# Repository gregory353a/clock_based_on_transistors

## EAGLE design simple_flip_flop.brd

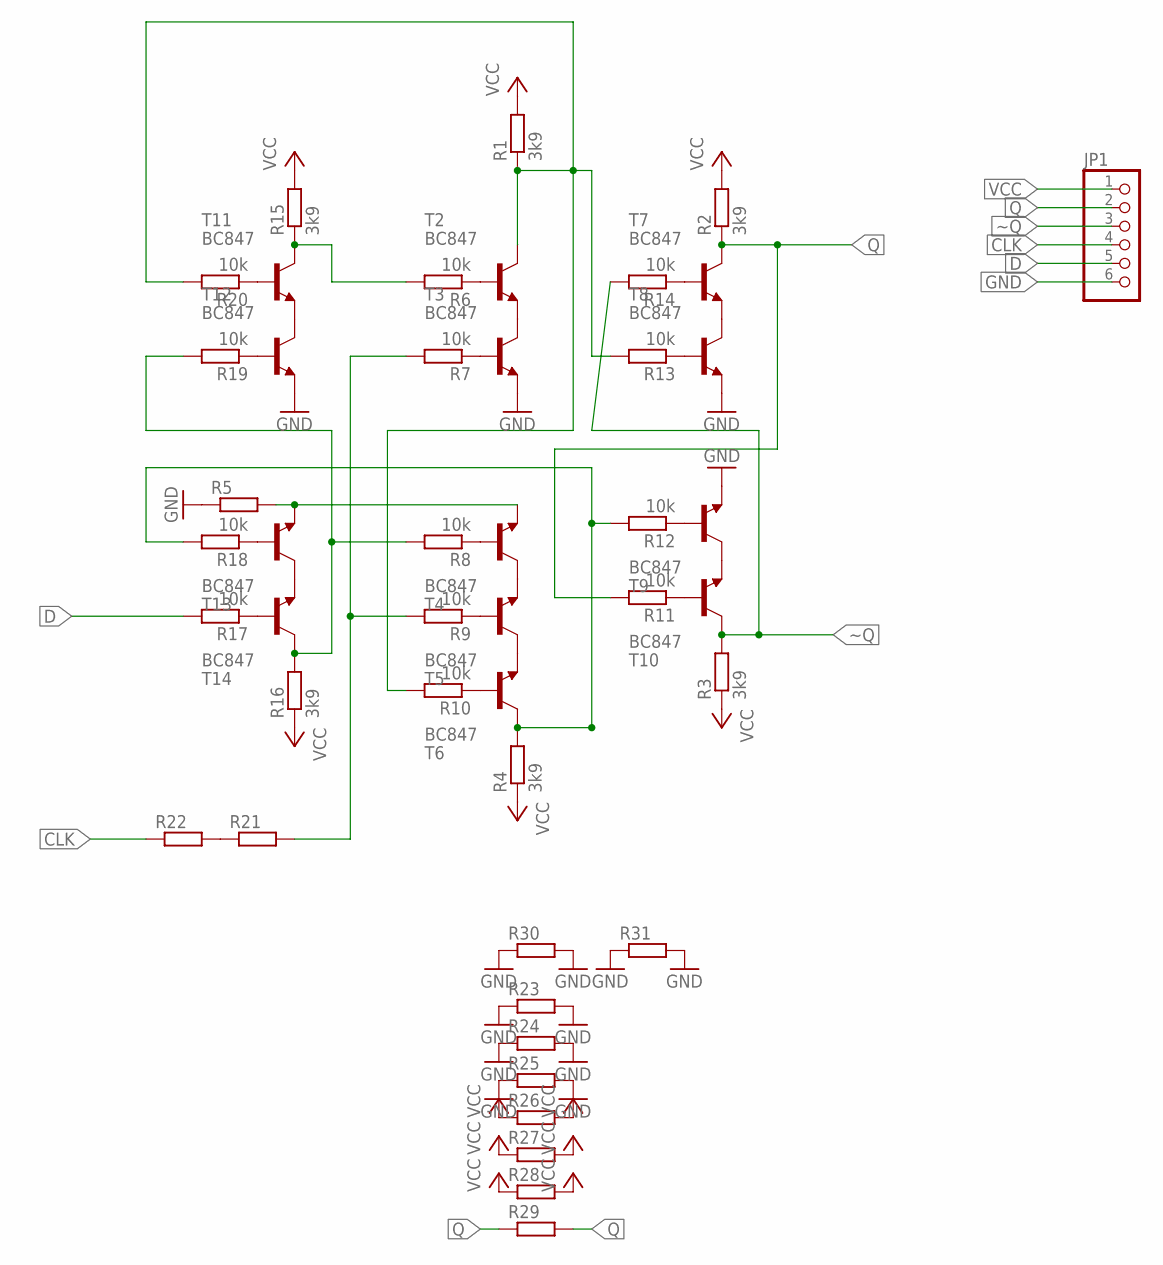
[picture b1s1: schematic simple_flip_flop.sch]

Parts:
JP1: PINHD-1X06_2.54-SMD; 1X06SMD
R1, R2, R3, R4, R15, R16: 3k9; R0805W
R5, R21, R22, R23, R24, R25, R26, R27, R28, R29, R30, R31: R-EU_R1206; R1206
R6, R7, R8, R9, R10, R11, R12, R13, R14, R17, R18, R19, R20: 10k; R0805W
T2, T3, T4, T5, T6, T7, T8, T9, T10, T11, T12, T13, T14: BC847; SOT23

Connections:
CLK: JP1.4, R22.1
D: JP1.5, R17.2
GND: JP1.6, R5.1, R23.1, R23.2, R24.1, R24.2, R25.1, R25.2, R30.1, R30.2, R31.1, R31.2, T3.2 (E), T8.2 (E), T9.2 (E), T12.2 (E)
unnamed: R5.2, T4.2 (E), T13.2 (E)
unnamed: T2.2 (E), T3.3 (C)
unnamed: T4.3 (C), T5.2 (E)
unnamed: T5.3 (C), T6.2 (E)
unnamed: T7.2 (E), T8.3 (C)
unnamed: T9.3 (C), T10.2 (E)
unnamed: R1.1, R10.2, R13.2, R20.2, T2.3 (C)
unnamed: R21.1, R22.2
unnamed: R4.2, R12.2, R18.2, T6.3 (C)
unnamed: R6.1, T2.1 (B)
unnamed: R7.1, T3.1 (B)
unnamed: R8.1, T4.1 (B)
unnamed: R9.1, T5.1 (B)
unnamed: R10.1, T6.1 (B)
unnamed: R11.1, T10.1 (B)
unnamed: R12.1, T9.1 (B)
unnamed: R13.1, T8.1 (B)
unnamed: R14.1, T7.1 (B)
unnamed: T11.2 (E), T12.3 (C)
unnamed: T13.3 (C), T14.2 (E)
unnamed: R6.2, R15.1, T11.3 (C)
unnamed: R8.2, R16.2, R19.2, T14.3 (C)
unnamed: R17.1, T14.1 (B)
unnamed: R18.1, T13.1 (B)
unnamed: R19.1, T12.1 (B)
unnamed: R20.1, T11.1 (B)
Q: JP1.2, R2.1, R11.2, R29.1, R29.2, T7.3 (C)
S%9: R7.2, R9.2, R21.2
VCC: JP1.1, R1.2, R2.2, R3.1, R4.1, R15.2, R16.1, R26.1, R26.2, R27.1, R27.2, R28.1, R28.2
~Q: JP1.3, R3.2, R14.2, T10.3 (C)

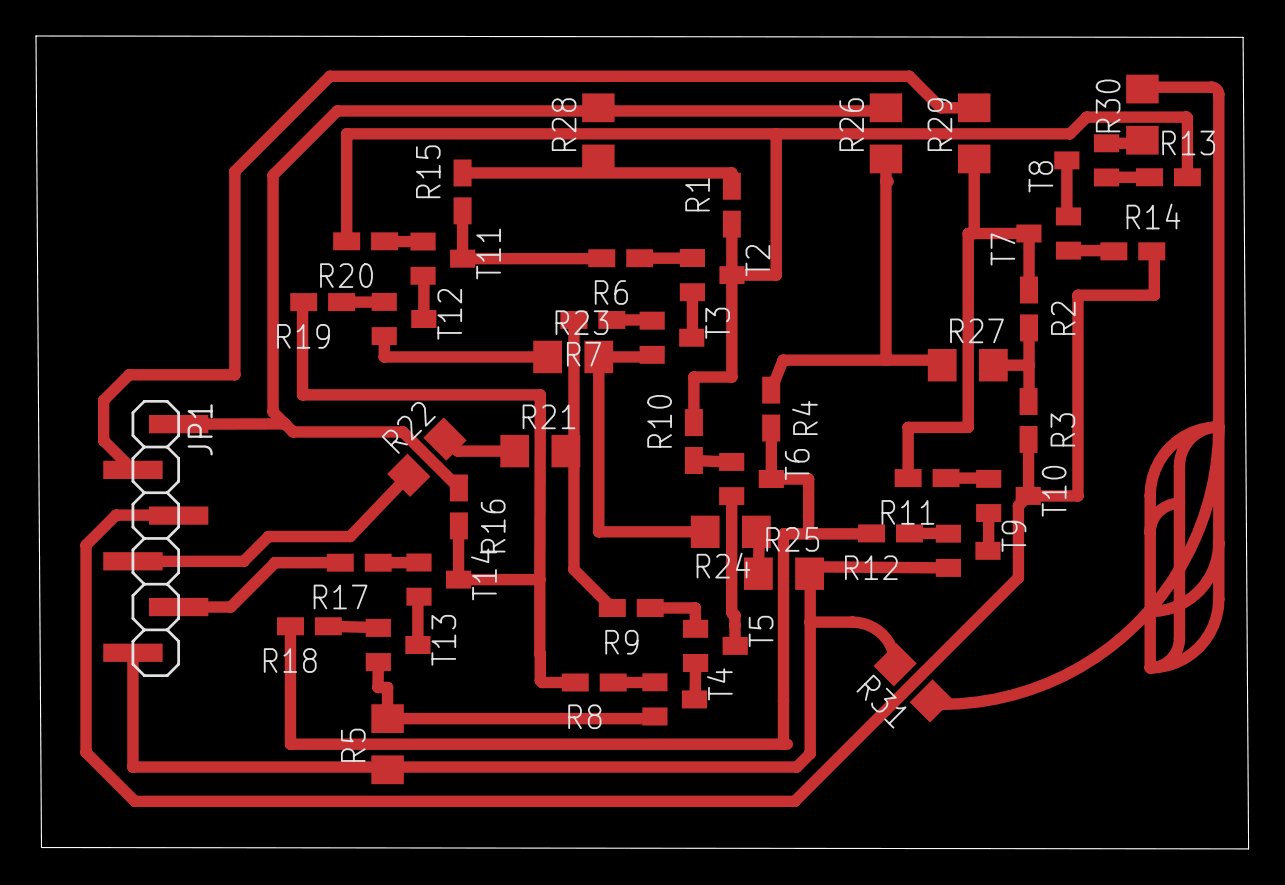
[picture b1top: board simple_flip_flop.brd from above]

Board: 2 copper layers, 67.4 x 45.2 mm, 45 parts (0 on the bottom side), 33 nets.

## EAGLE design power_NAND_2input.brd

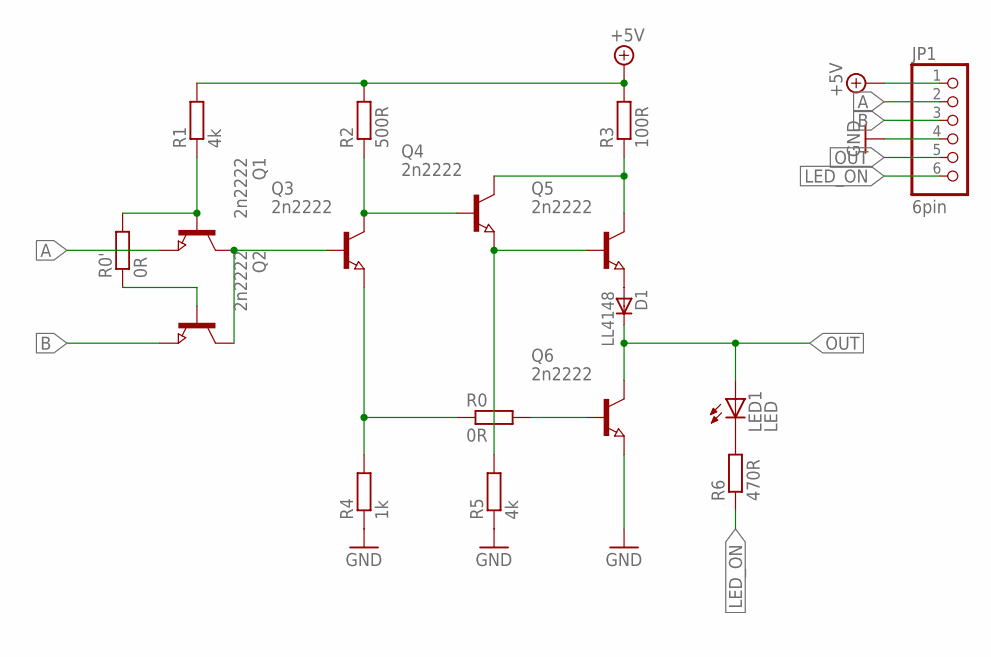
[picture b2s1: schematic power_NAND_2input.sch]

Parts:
D1: LL4148; SOD80_DO213AA_MINIMELF
JP1: 6pin; 1X06SMD/90
LED1: LED; CHIPLED_0805
Q1, Q2, Q3, Q4, Q5, Q6: 2n2222; SOT23
R0, R0': 0R; R1206
R1, R5: 4k; R0805
R2: 500R; R0805
R3: 100R; R0805
R4: 1k; R0805
R6: 470R; R0805

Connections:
+5V: JP1.1, R1.2, R2.2, R3.2
A: JP1.2, Q1.2 (E)
B: JP1.3, Q2.2 (E)
GND: JP1.4, Q6.2 (E), R4.1, R5.1
LED_ON: JP1.6, R6.1
unnamed: Q1.3 (C), Q2.3 (C), Q3.1 (B)
unnamed: Q1.1 (B), R0'.2, R1.1
unnamed: Q3.3 (C), Q4.1 (B), R2.1
unnamed: Q3.2 (E), R0.1, R4.2
unnamed: Q4.3 (C), Q5.3 (C), R3.1
unnamed: Q4.2 (E), Q5.1 (B), R5.2
unnamed: D1.A, Q5.2 (E)
unnamed: Q2.1 (B), R0'.1
unnamed: LED1.C, R6.2
unnamed: Q6.1 (B), R0.2
OUT: D1.C, JP1.5, LED1.A, Q6.3 (C)

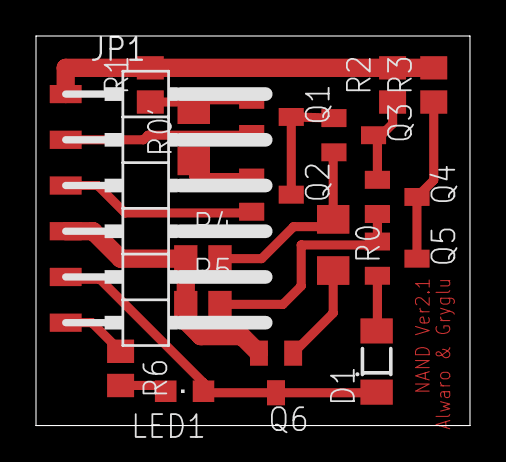
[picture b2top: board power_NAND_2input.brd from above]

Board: 2 copper layers, 24.1 x 21.6 mm, 17 parts (0 on the bottom side), 16 nets.

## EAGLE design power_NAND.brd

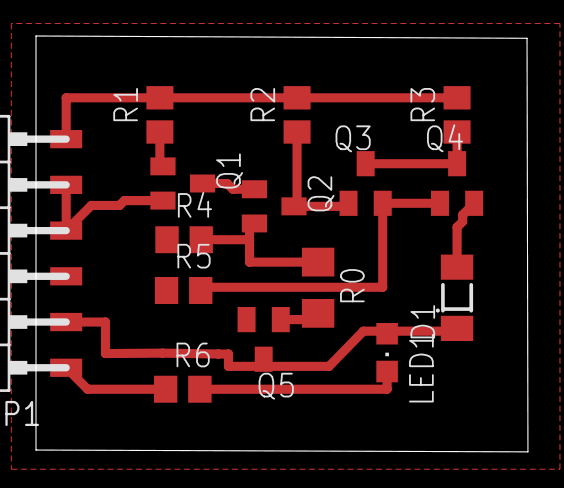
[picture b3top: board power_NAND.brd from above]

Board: 2 copper layers, 27.3 x 23.1 mm, 15 parts (0 on the bottom side), 14 nets.

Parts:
D1: LL4148; SOD80_DO213AA_MINIMELF
JP1: 1X06SMD/90
LED1: CHIPLED_0805
Q1, Q2, Q3, Q4, Q5: 2n2222; SOT23
R0: 0R; R1206
R1, R5: 4k; R0805
R2: 500R; R0805
R3: 100R; R0805
R4: 1k; R0805
R6: 470R; R0805

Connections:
+5V: JP1.6, R1.2, R2.2, R3.2
GND: JP1.3, Q5.2, R4.1, R5.1
unnamed: Q1.1, R1.1
unnamed: Q2.3, Q3.1, R2.1
unnamed: Q2.2, R0.1, R4.2
unnamed: Q3.3, Q4.3, R3.1
unnamed: Q3.2, Q4.1, R5.2
unnamed: D1.A, Q4.2
unnamed: JP1.4, JP1.5, Q1.2
POWER_ON: JP1.1, R6.1
S$2: Q5.1, R0.2
S$3: LED1.C, R6.2
S$4: Q1.3, Q2.1
S$6: D1.C, JP1.2, LED1.A, Q5.3

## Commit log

2018-03-06 init commit, git ignore
2018-03-06 power_NAND schemat, board, project
2018-03-07 board doesn't remember ground plane
2018-03-08 new prototype power nand gate with two transistors on the input
2018-03-10 new design for power_nand
2018-03-10 schemat for simple flip flop type D
2018-03-10 prototype board simple_flip_flop
2023-07-19 add project file
